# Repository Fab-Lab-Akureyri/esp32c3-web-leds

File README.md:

# esp32c3-web-leds

## Tilgangur

Búa til viðbót við [Fab Xiao bretti FLA](https://github.com/Fab-Lab-Akureyri/fla-xiao) (útgáfa af bretti [Adrian Torres](https://fabacademy.org/2020/labs/leon/students/adrian-torres/fabxiao.html)). 

Notast við [74HCT164 shift register](https://www.diodes.com/assets/Datasheets/74HCT164.pdf) til að keyra 8 LED á einum útgangspinna. 

Tengist WiFi og hægt að kveikja og slökkva á hverju LED-i fyrir sig í vefviðmóti. 

## Myndir

Ath: Guli vírinn er útaf "prótótýpu", ekki skv teikningu =)

## Kóði

Skrifað í VSCode með Platform.io, en ætti að nægja að afrita úr main.cpp í Arduino IDE. 

Ath, bæta esp32c3 við Arduino IDE, sjá t.d. [hér](https://dev.to/rafalozan0/esp32-c3-12f-using-the-arduino-ide-getting-started-environment-setup-38ij). 

Kóði byggður á [þessu](https://www.instructables.com/Web-Controlled-Desk-Lamp-With-XIAO-ESP32-C3/).

## KiCad

Rafrásin er búin til í KiCad, sjá `shifter` möppuna. 

## BOM

|   Íhlutir |   Týpa    |   Fjöldi  |
|   ---     |   ---     |   ---     |
| [74HCT164N](https://www.digikey.com/en/products/detail/nxp-usa-inc/74hct164n-652/763124)              |   Stjakgisti  |   1   |
| [LED](https://www.digikey.com/en/products/detail/w%C3%BCrth-elektronik/150120BS75000/4489933)         |   Viðnám      |   8   |
| [0Ω](https://www.digikey.com/en/products/detail/yageo/RC1206FR-070RL/5698945)                         |   Viðnám      |   3   |
| [100Ω](https://www.digikey.com/en/products/detail/yageo/RC1206FR-07100RL/728491)                      |   Viðnám      |   8   |
| [1x05](https://www.digikey.com/en/products/detail/sullins-connector-solutions/GBC36SGSN-M89/862355)   |   Pinnatengi  |   1   |

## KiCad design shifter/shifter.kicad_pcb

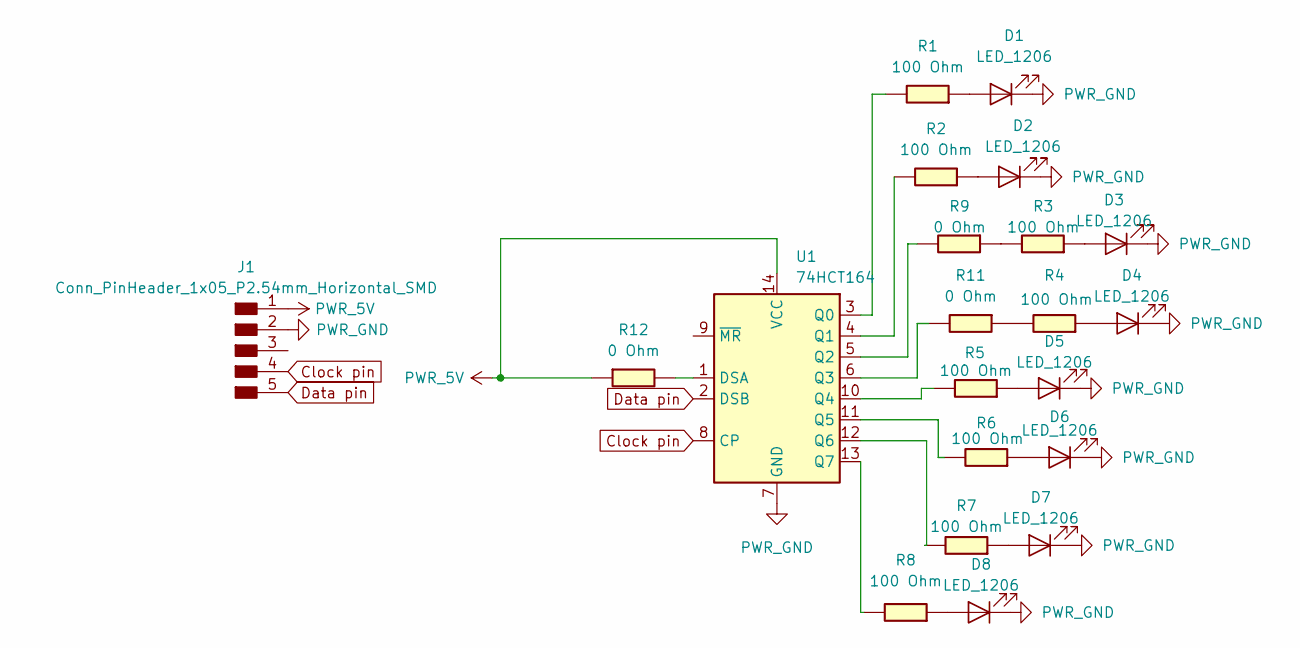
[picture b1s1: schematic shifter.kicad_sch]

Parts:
D1, D2, D3, D4, D5, D6, D7, D8: LED_1206
J1: Conn_PinHeader_1x05_P2.54mm_Horizontal_SMD; PinHeader_1x05_P2.54mm_Horizontal_SMD
R1, R2, R3, R4, R5, R6, R7, R8: 100 Ohm; R_1206
R9, R11, R12: 0 Ohm; R_1206
U1: 74HCT164; DIP-14_W7.62mm

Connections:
Clock pin: J1.4, U1.8 (CP)
Data pin: J1.5, U1.2 (DSB)
unnamed: D1.2 (A), R1.2
unnamed: D2.2 (A), R2.2
unnamed: D3.2 (A), R3.2
unnamed: D4.2 (A), R4.2
unnamed: D5.2 (A), R5.2
unnamed: D6.2 (A), R6.2
unnamed: D7.2 (A), R7.2
unnamed: D8.2 (A), R8.2
unnamed: R3.1, R9.2
unnamed: R4.1, R11.2
unnamed: R12.1, U1.1 (DSA)
unnamed: R1.1, U1.3 (Q0)
unnamed: R2.1, U1.4 (Q1)
unnamed: R9.1, U1.5 (Q2)
unnamed: R11.1, U1.6 (Q3)
unnamed: R5.1, U1.10 (Q4)
unnamed: R6.1, U1.11 (Q5)
unnamed: R7.1, U1.12 (Q6)
unnamed: R8.1, U1.13 (Q7)
PWR_5V: J1.1, R12.2, U1.14 (VCC)
PWR_GND: D1.1 (K), D2.1 (K), D3.1 (K), D4.1 (K), D5.1 (K), D6.1 (K), D7.1 (K), D8.1 (K), J1.2, U1.7 (GND)

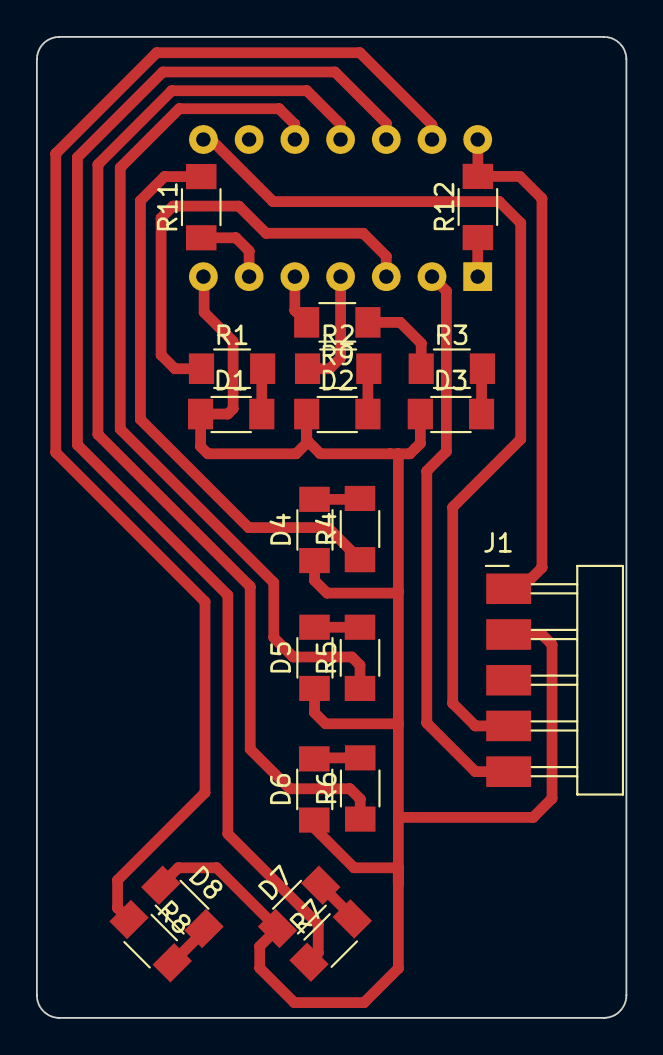
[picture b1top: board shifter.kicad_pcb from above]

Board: 2 copper layers, 32.8 x 54.5 mm, 21 parts (1 on the bottom side), 23 nets.

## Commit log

2023-09-12 Adding .gitignore
2023-09-12 Added source code
2023-09-12 Updated .gitignore for KiCad
2023-09-12 Add KiCad project
2023-09-12 Typo
